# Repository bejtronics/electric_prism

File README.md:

# electric_prism
Files for the Electric Prism. 
More information available at http://www.bejtronics.com/electric-prism/

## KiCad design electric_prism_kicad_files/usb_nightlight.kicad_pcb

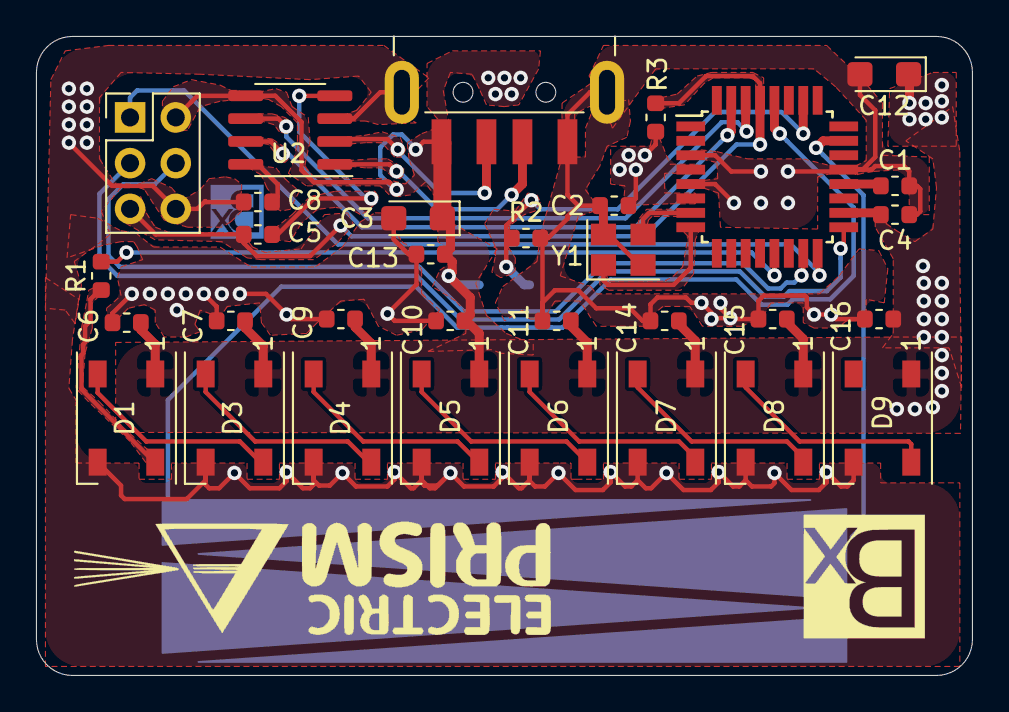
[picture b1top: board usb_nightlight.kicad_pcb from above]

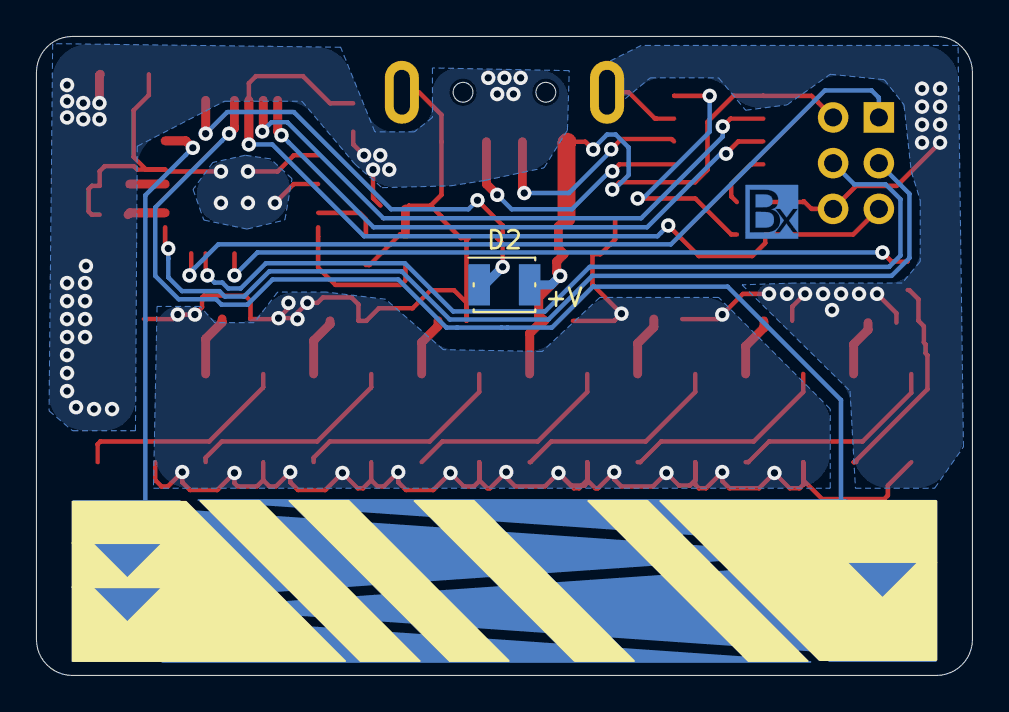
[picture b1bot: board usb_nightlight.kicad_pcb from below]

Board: 2 copper layers, 52.0 x 35.5 mm, 34 parts (2 on the bottom side), 27 nets.

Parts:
C1, C2, C5, C6, C7, C8, C9, C10, C11, C13, C14, C15, C16: 100n; C_0603_1608Metric
C3, C12: 4.7u; CP_EIA-3216-12_Kemet-S
C4: 1u; C_0603_1608Metric
D1, D3, D4, D5, D6, D7, D8, D9: WS2812B; LED_WS2812B_PLCC4_5.0x5.0mm_P3.2mm
D2: D_Photo; 3528_two_pin
J1: Conn_02x03_Odd_Even; PinHeader_2x03_P2.54mm_Vertical
J2: USB_A; USB_A_CNCTech_1001-011-01101_Horizontal
R1: 430; R_0603_1608Metric
R2, R3: 10k; R_0603_1608Metric
SW1: CAP SLIDER; cap_slider_9x40
U1: ATmega328P-AU; TQFP-32_7x7mm_P0.8mm
U2: CH330N; SOIC-8_3.9x4.9mm_P1.27mm
Y1: Crystal; Crystal_SMD_3225-4Pin_3.2x2.5mm

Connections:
+5V: C2.1, C3.1, C4.2, C6.2, C7.2, C9.2, C10.2, C11.2, C12.1, C13.1, C14.2, C15.2, C16.2, D1.1, D2.2, D3.1, D4.1, D5.1, D6.1, D7.1, D8.1, D9.1, J1.2, J2.1, R3.1, U1.4, U1.6, U1.18, U2.5
GND: C1.2, C2.2, C3.2, C4.1, C6.1, C7.1, C8.2, C9.1, C10.1, C11.1, C12.2, C13.2, C14.1, C15.1, C16.1, D1.3, D3.3, D4.3, D5.3, D6.3, D7.3, D8.3, D9.3, J1.6, J2.4, J2.5, R2.2, U1.3, U1.5, U1.21, U2.3, Y1.2, Y1.4
MISO: J1.1, U1.16
MOSI: J1.4, U1.15
unnamed: C1.1, U1.20
unnamed: C5.2, U2.4
unnamed: C8.1, U2.8
unnamed: D1.2, D3.4
unnamed: D1.4, R1.1
unnamed: D2.1, R2.1, U1.26
unnamed: D3.2, D4.4
unnamed: D4.2, D5.4
unnamed: D5.2, D6.4
unnamed: D6.2, D7.4
unnamed: D7.2, D8.4
unnamed: D8.2, D9.4
unnamed: J2.2, U2.2
unnamed: J2.3, U2.1
unnamed: R1.2, U1.13
unnamed: U1.7, Y1.3
unnamed: U1.8, Y1.1
unnamed: U1.30, U2.6
unnamed: U1.31, U2.7
RST: C5.1, J1.5, R3.2, U1.29
SCK: J1.3, U1.17
SLIDER_1: SW1.1, U1.23
SLIDER_2: SW1.2, U1.28

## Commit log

2021-02-13 Add files via upload
    Updated design:
    - Fixed asymmetry
    - Added pullup resistor to reset line
    - Made curvy copper pours
2021-02-13 Add files via upload
    Updated design:
    - Fixed asymmetry
    - Added pull-up resistor to reset line
    - Made curvy copper pours
